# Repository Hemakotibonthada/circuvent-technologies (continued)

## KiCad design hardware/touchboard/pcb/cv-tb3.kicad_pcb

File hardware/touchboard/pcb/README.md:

# Touch Switchboard PCB - KiCad project + fab checklist

Design source: SCHEMATIC.md (netlist) + BOM.csv. Open cv-tb3.kicad_pro in KiCad, capture, lay out, export.

## Board spec
- 2-layer FR4, 1.6 mm, HASL lead-free, 2 oz copper on mains.
- >= 8 mm creepage / 6 mm clearance mains-to-LV; isolation slots.
- Size target ~ 80 x 60 mm (3-gang plate); 4x M3.
- Touch pads on the top copper under the plate; guard ring around each.

## Pre-fab (DFM) checklist
- [ ] ERC/DRC clean at fab rules; mains clearances as keepout
- [x] **Metering isolation resolved** — U6 runs on MTR_VDD/MTR_GND from T1's
      third winding, and CF/CF1/SEL cross through U7/U8/U9. No SELV net
      reaches the metering chip.
- [ ] Confirm T1's third winding (pins 7-8) is specified to the winding house
      with the same reinforced insulation as the main secondary
- [ ] Only T1, CY1, U3/U4/U5 and U7/U8/U9 cross the barrier — check the plot
- [ ] Fuse + MOV at entry; single L-bus to all three relay COMs
- [ ] Kelvin sense pair on Rsh, short and paired
- [ ] Per-gang derating on silk; total <= fuse/PSU/copper
- [ ] Test points: 5V, 3V3, GND, IO25/26/33, IO4/15/13 (touch)
- [ ] UART/EN/IO0 pads for the flashing jig; fiducials

## Export for fab / assembly
- [ ] Gerbers + Excellon -> gerbers/; IPC-356 netlist
- [ ] BOM (BOM.csv) + CPL/centroid; PDF assembly + 3D STEP
- [ ] Order boards + stencil

## Bring-up (EVT)
- [ ] Rails before ESP32; flash test firmware over jig
- [ ] All three relays click + switch; touch pads toggle offline
- [ ] Backlight dims across the full 0-100 range
- [ ] Metering reads V/A/W/PF against a reference load
- [ ] Cloud sync self-test; schedule fires

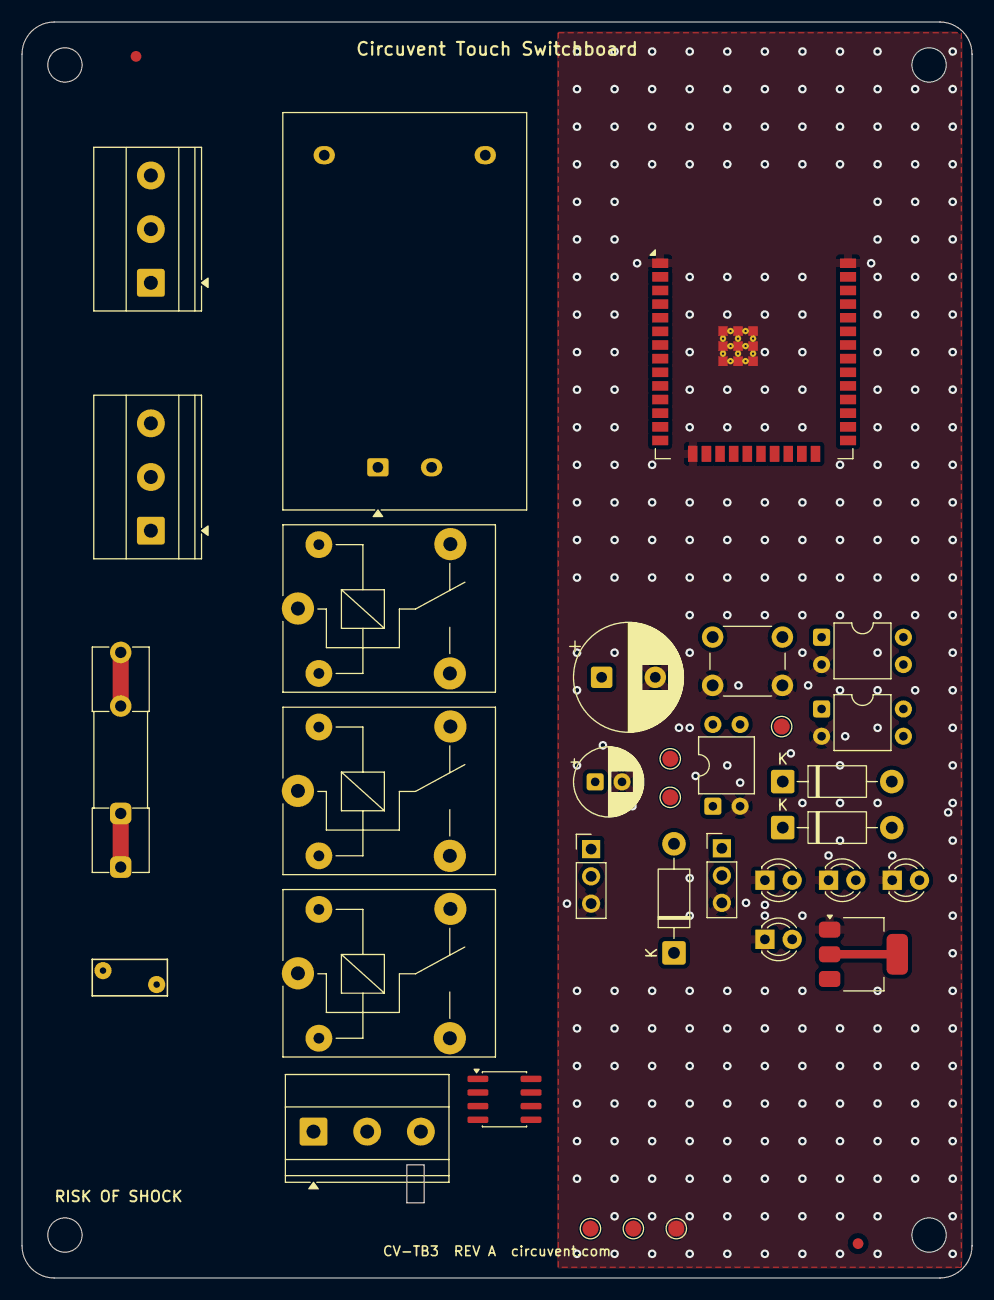
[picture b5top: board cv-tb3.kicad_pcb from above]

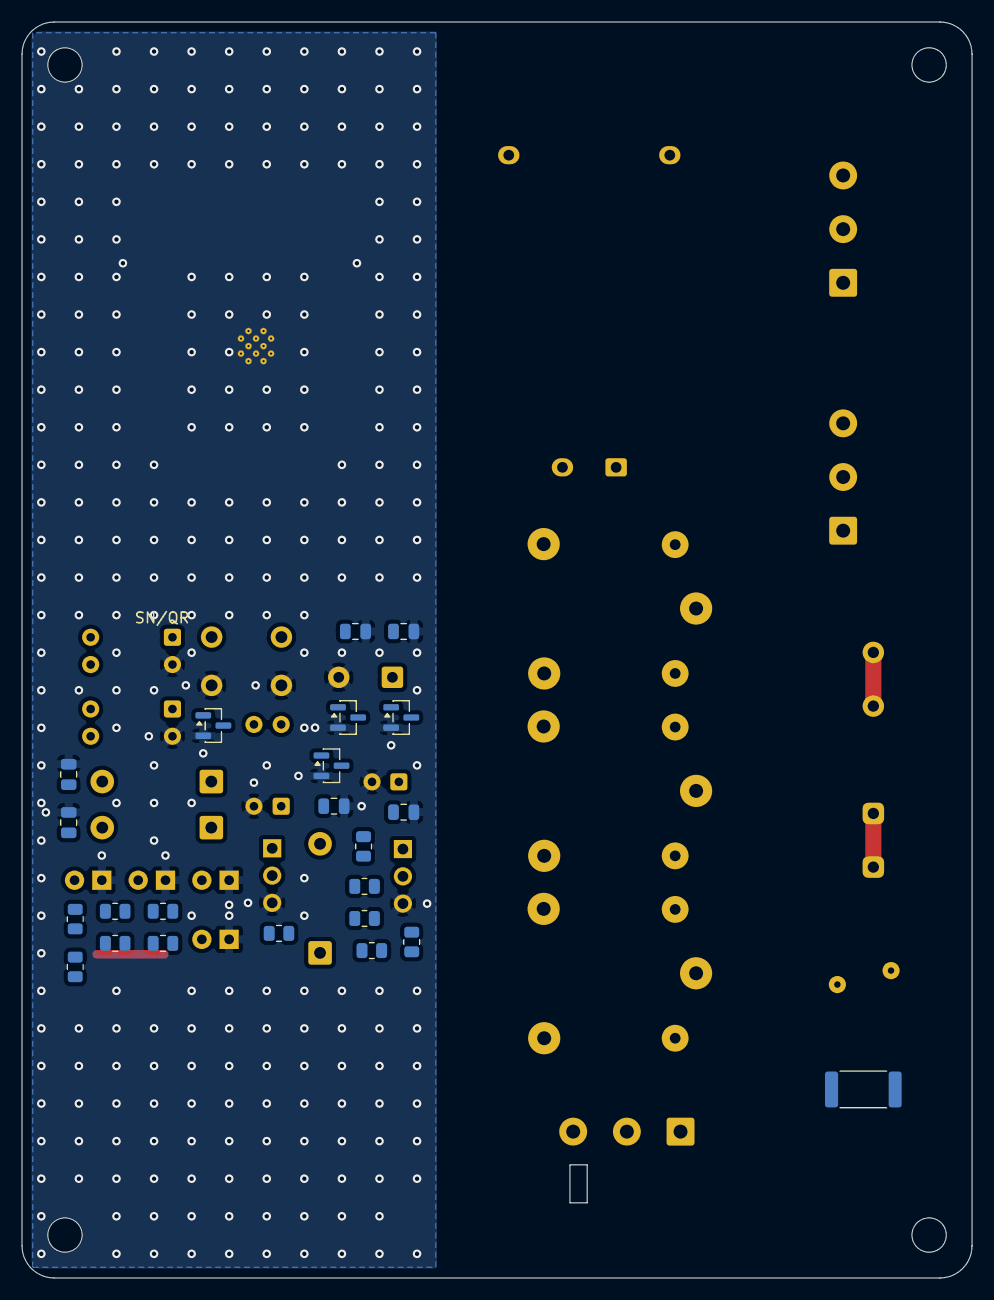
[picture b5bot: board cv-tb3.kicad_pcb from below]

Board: 2 copper layers, 88.5 x 117.0 mm, 62 parts (23 on the bottom side), 39 nets.

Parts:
C1: 470uF/10V; CP_Radial_D10.0mm_P5.00mm
C2: 100uF/6.3V; CP_Radial_D6.3mm_P2.50mm
C3, C4, C5, C6, C7, C8: 100nF; C_0805_2012Metric
D1, D2, D3: 1N4007; D_DO-41_SOD81_P10.16mm_Horizontal
F1: 6A slow-blow; Fuseholder_Clip-5x20mm_Littelfuse_111_Inline_P20.00x5.00mm_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
FID1, FID2: Fiducial; Fiducial_1mm_Mask2mm
J1: 2P 5.08mm; TerminalBlock_Phoenix_MKDS-1,5-3_1x03_P5.00mm_Horizontal
J2, J3: 3P 5.08mm; TerminalBlock_Phoenix_MKDS-1,5-3_1x03_P5.00mm_Horizontal
J4: 3P 2.54mm; PinHeader_1x03_P2.54mm_Vertical
JP: 3P 2.54mm; PinHeader_1x03_P2.54mm_Vertical
K1, K2, K3: SRD-05VDC-SL-C; Relay_SPDT_SANYOU_SRD_Series_Form_C
LED0: Green 3mm; LED_D3.0mm
LED1, LED2, LED3: Blue 3mm; LED_D3.0mm
MH1, MH2, MH3, MH4: MountingHole; MountingHole_3.2mm_M3
PS1: HLK-PM03 (5V 3W); Converter_ACDC_Hi-Link_HLK-PMxx
Q1, Q2, Q3, Q4: S8050; SOT-23
R1, R2, R3, R4, R5, R6, R7, R8, R9, R10, R11, R12: 10k/1k/330; R_0805_2012Metric
RV1: 7D471K; RV_Disc_D7mm_W3.4mm_P5mm
Rsh: 1mR 2W; R_2512_6332Metric
SW1: 6mm tactile; SW_PUSH_6mm_H5mm
TP1, TP2, TP3: Copper pad + decal; TestPoint_Pad_D1.5mm
TP4: +5V; TestPoint_Pad_D1.5mm
TP5: +3V3; TestPoint_Pad_D1.5mm
TP6: GND; TestPoint_Pad_D1.5mm
U1: ESP32-WROOM-32E (4MB); ESP32-WROOM-32E
U2: AMS1117-3.3; SOT-223-3_TabPin2
U3, U4, U5: PC817; DIP-4_W7.62mm
U6: BL0937 / HLW8012; SOIC-8_3.9x4.9mm_P1.27mm

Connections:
+3V3: C2.1, C3.1, C4.1, C5.1, C6.1, C7.1, C8.1, R8.1, R9.1, TP5.1, U1.2, U2.2, U6.8
+5V: C1.1, D1.1, D2.1, D3.1, J3.1, J4.1, K1.2, K2.2, K3.2, PS1.4, TP4.1, U2.3, U3.4, U4.4, U5.4
AC_L: F1.1, J1.1
AC_LOAD: J1.3, J2.1, Rsh.2, U6.3
AC_L_FUSED: F1.2, K1.1, K2.1, K3.1, PS1.1, RV1.1, U6.1
AC_N: J1.2, J2.3, J3.3, PS1.2, RV1.2
BACKLIGHT: R7.1, U1.29
BACKLIGHT_B: Q4.1, R7.2
BACKLIGHT_OUT: J4.2, Q4.3
BTN_PIN: SW1.1, U1.25
EN: R8.2, U1.3
GND: C1.2, C2.2, C3.2, C4.2, C5.2, C6.2, C7.2, C8.2, J4.3, JP.3, LED0.1, LED1.1, LED2.1, LED3.1, PS1.3, Q1.2, Q2.2, Q3.2, Q4.2, SW1.2, TP6.1, U1.1, U1.15, U1.38, U1.39, U2.1, U3.2, U4.2, U5.2, U6.4
LED0_A: LED0.2, R9.2
MTR_CF: U1.6, U6.5
MTR_CF1: U1.7, U6.6
MTR_SEL: U1.30, U6.7
RELAY1: R1.1, R2.1, U1.10
RELAY1_A: LED1.2, R2.2
RELAY1_COIL: D1.2, K1.5, Q1.3
RELAY1_DRV: Q1.1, U3.3
RELAY1_OPT: R1.2, U3.1
RELAY1_SW: K1.3, Rsh.1, U6.2
RELAY2: R3.1, R4.1, U1.11
RELAY2_A: LED2.2, R4.2
RELAY2_COIL: D2.2, K2.5, Q2.3
RELAY2_DRV: Q2.1, U4.3
RELAY2_OPT: R3.2, U4.1
RELAY2_SW: J2.2, K2.3
RELAY3: R5.1, R6.1, U1.9
RELAY3_A: LED3.2, R6.2
RELAY3_COIL: D3.2, K3.5, Q3.3
RELAY3_DRV: Q3.1, U5.3
RELAY3_OPT: R5.2, U5.1
RELAY3_SW: J3.2, K3.3
TOUCH1__T0: TP1.1, U1.26
TOUCH2__T3: TP2.1, U1.23
TOUCH3__T4: TP3.1, U1.16
UART_RX: JP.2, U1.34
UART_TX: JP.1, U1.35

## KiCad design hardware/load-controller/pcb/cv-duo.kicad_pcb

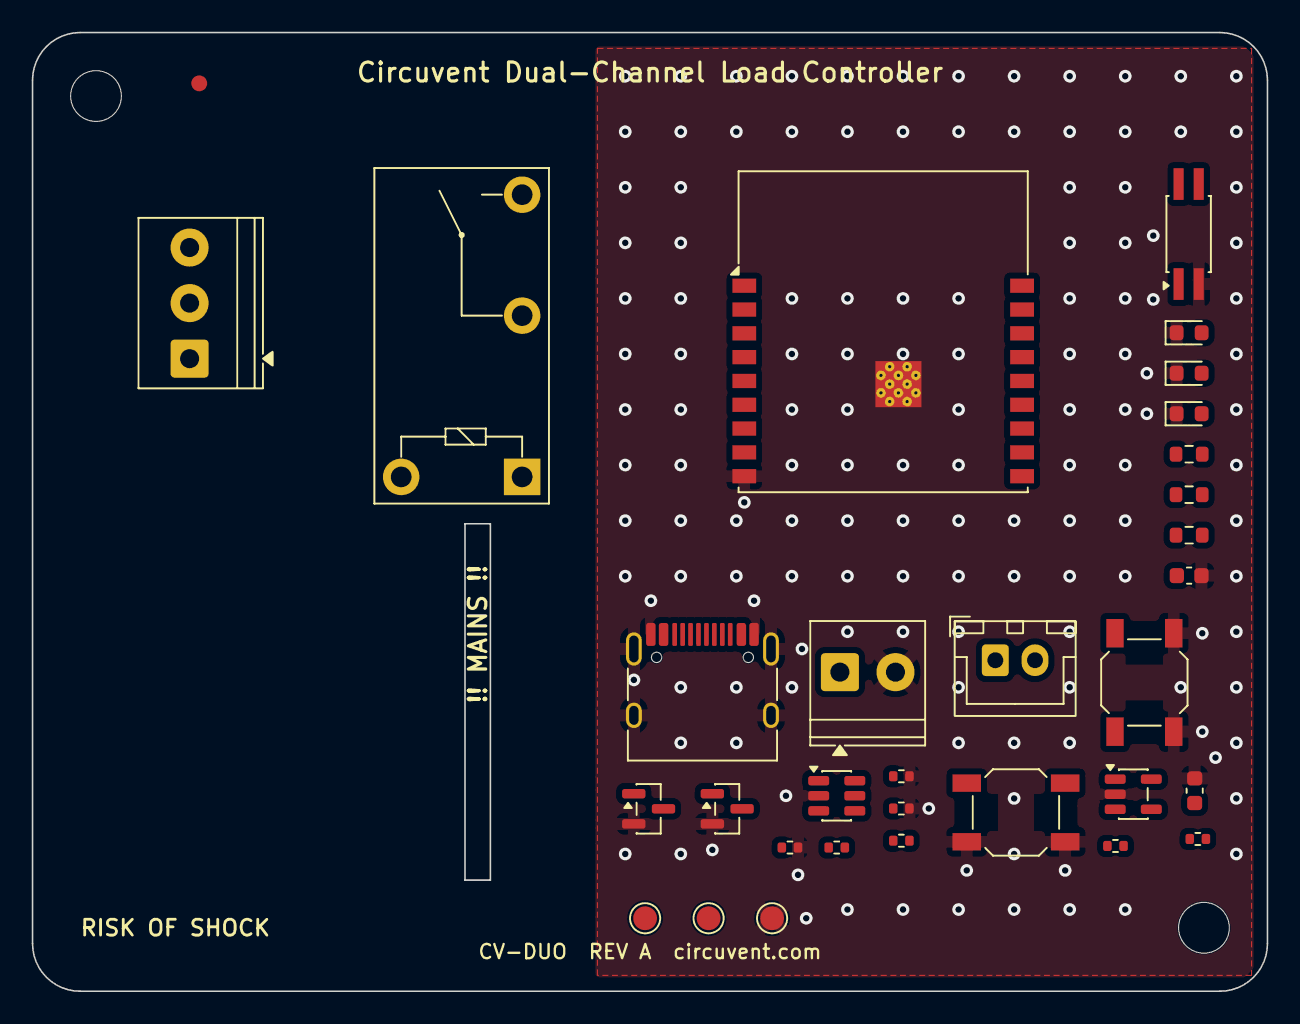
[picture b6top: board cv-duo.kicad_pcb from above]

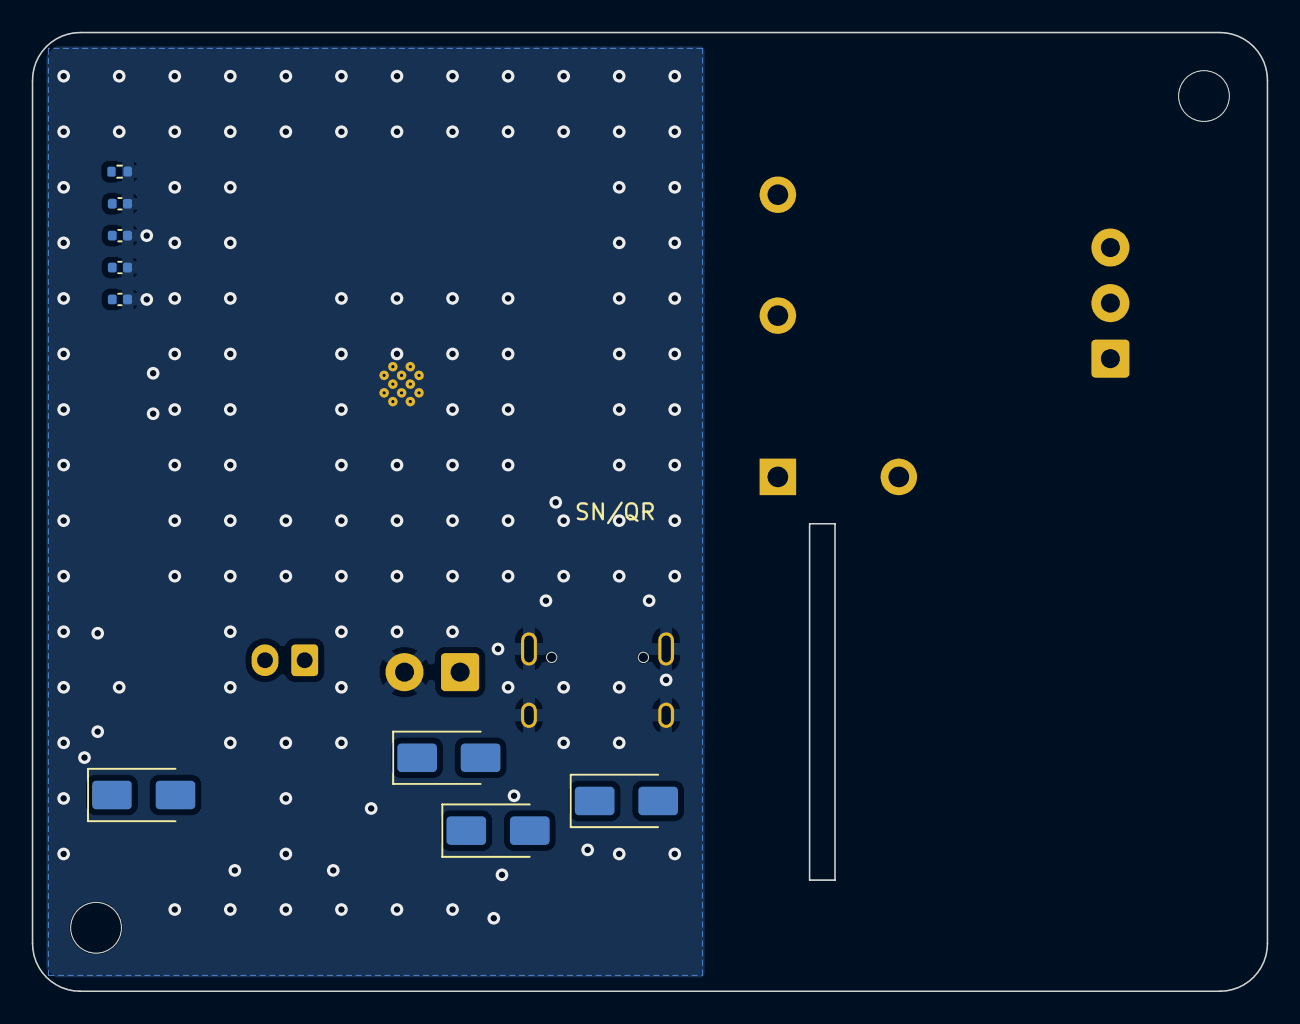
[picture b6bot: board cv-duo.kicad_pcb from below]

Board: 2 copper layers, 77.8 x 60.4 mm, 43 parts (9 on the bottom side), 25 nets, no tracks yet.

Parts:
C1, C3: 10u; C_0603_1608Metric
C2, C4, C5, C6: 100n; C_0402_1005Metric
D1, D2, D3, D4: SS14; D_SMA
FID1: Fiducial; Fiducial_1mm_Mask2mm
J1: USB-C 16P receptacle; USB_C_Receptacle_HRO_TYPE-C-31-M-12
J2: 5V DC input; TerminalBlock_Phoenix_PT-1,5-2-3.5-H_1x02_P3.50mm_Horizontal
J3: Relay load out (mains); TerminalBlock_Phoenix_PT-1,5-3-3.5-H_1x03_P3.50mm_Horizontal
J4: Pulse output; JST_XH_B2B-XH-A_1x02_P2.50mm_Vertical
K1: Omron G5Q-1A 5VDC; Relay_SPST_Omron-G5Q-1A
LED1: Green; LED_0603_1608Metric
LED2: Red; LED_0603_1608Metric
LED3: Blue; LED_0603_1608Metric
MH1, MH2: MountingHole; MountingHole_3.2mm_M3
PC1: LTV-817S; SO-4_4.4x2.3mm_P1.27mm
Q1, Q2: AO3400A; SOT-23
R1, R2: 5.1k; R_0402_1005Metric
R3, R4, R6: 10k; R_0402_1005Metric
R5: 1k; R_0402_1005Metric
R7: 100R; R_0402_1005Metric
R8: 100k; R_0402_1005Metric
R9, R10, R11: 1k; R_0603_1608Metric
SW1: RESET tactile; SW_SPST_SKQG_WithoutStem
SW2: BOOT tactile; SW_SPST_SKQG_WithoutStem
TP1: +5V; TestPoint_Pad_D1.5mm
TP2: +3V3; TestPoint_Pad_D1.5mm
TP3: GND; TestPoint_Pad_D1.5mm
U1: ESP32-C3-WROOM-02 (4MB); ESP32-C3-WROOM-02
U2: AP2112K-3.3; SOT-23-5
U3: USBLC6-2SC6; SOT-23-6

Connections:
+3V3: C3.1, C4.1, C5.1, PC1.4, R3.1, R4.1, R9.1, TP2.1, U1.1, U2.5
+5V: C1.1, C2.1, D1.1, D2.1, D3.1, D4.1, J4.1, K1.1, TP1.1, U2.1, U2.3
BOOT_N: R4.2, SW2.1, U1.8
CC1: J1.A5, R1.1
CC2: J1.B5, R2.1
EN: C6.1, R3.2, SW1.1, U1.2
GND: C1.2, C2.2, C3.2, C4.2, C5.2, C6.2, J1.A1, J1.A12, J1.B1, J1.B12, J1.SH, J2.2, LED1.1, LED2.1, LED3.1, PC1.2, Q1.2, Q2.2, R1.2, R2.2, R6.2, R8.2, SW1.2, SW2.2, TP3.1, U1.9, U1.19, U2.2, U3.2
LOAD_COM: J3.1, K1.2
LOAD_NO: J3.2, K1.3
PULSE_GATE: Q2.1, R7.2, R8.1
PULSE_LED: R11.1, U1.6
PULSE_LED_A: LED3.2, R11.2
PULSE_OUT: D4.2, J4.2, Q2.3
PULSE_PWM: R7.1, U1.4
PWR_LED_A: LED1.2, R9.2
RELAY_COIL: D3.2, K1.5, Q1.3
RELAY_CTL: R5.1, U1.3
RELAY_GATE: PC1.3, Q1.1, R6.1
RELAY_LED: R10.1, U1.5
RELAY_LED_A: LED2.2, R10.2
RELAY_OPT: PC1.1, R5.2
USB_D_N: J1.A7, J1.B7, U1.13, U3.1, U3.6
USB_D_P: J1.A6, J1.B6, U1.14, U3.3, U3.4
VBUS: D1.2, J1.A4, J1.A9, J1.B4, J1.B9, U3.5
VIN_EXT: D2.2, J2.1

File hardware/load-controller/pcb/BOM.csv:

Ref,Qty,Value/Part,Package,Description,Notes
U1,1,ESP32-C3-WROOM-02 (4MB),ESP32-C3,Wi-Fi/BLE RISC-V MCU module,Native USB on IO18/IO19
U2,1,AP2112K-3.3,SOT-23-5,5V -> 3.3V 600mA LDO,MCU rail
U3,1,USBLC6-2SC6,SOT-23-6,USB ESD protection array,On D+/D-/VBUS
PC1,1,LTV-817S,SO-4,Optocoupler CTR 50-600%,Isolates MCU from coil driver
K1,1,Omron G5Q-1A 5VDC,relay G5Q,SPST-NO 10A power relay,Channel 1 - switches the mains load
Q1,1,AO3400A,SOT-23,N-channel MOSFET 30V 5.7A,Relay coil driver
Q2,1,AO3400A,SOT-23,N-channel MOSFET 30V 5.7A,Channel 2 PWM low-side switch
D1,1,SS14,SMA,Schottky 40V 1A,USB VBUS OR-ing diode
D2,1,SS14,SMA,Schottky 40V 1A,Terminal 5V OR-ing diode
D3,1,SS14,SMA,Schottky 40V 1A,K1 coil flyback clamp
D4,1,SS14,SMA,Schottky 40V 1A,Channel 2 inductive clamp
J1,1,USB-C 16P receptacle,USB-C,5V power + native USB,Programming and debug
J2,1,5V DC input,term 3.5/2,3.5mm screw terminal 2P,Auxiliary 5V supply
J3,1,Relay load out (mains),term 3.5/3,3.5mm screw terminal 3P,COM / NO / PE - mains rated
J4,1,Pulse output,JST-XH/2,JST-XH 2-pin header,Channel 2 PWM out
SW1,1,RESET tactile,tactile SMD,3x4x2mm SMD tactile switch,Pulls EN low
SW2,1,BOOT tactile,tactile SMD,3x4x2mm SMD tactile switch,Pulls IO9 low
LED1,1,Green,0603LED,Power indicator,Always on from 3V3
LED2,1,Red,0603LED,Relay energised,IO6
LED3,1,Blue,0603LED,Pulse active,IO7
R1,1,5.1k,0402,USB-C CC1 pulldown,Sink advertisement
R2,1,5.1k,0402,USB-C CC2 pulldown,Sink advertisement
R3,1,10k,0402,EN pull-up,Reset RC with C6
R4,1,10k,0402,IO9 boot pull-up,
R5,1,1k,0402,PC1 LED series resistor,From IO4
R6,1,10k,0402,Q1 gate pulldown,Fail-safe off
R7,1,100R,0402,Q2 gate series resistor,Limits ringing
R8,1,100k,0402,Q2 gate pulldown,Fail-safe off
R9,1,1k,0603,LED1 series resistor,
R10,1,1k,0603,LED2 series resistor,
R11,1,1k,0603,LED3 series resistor,
C1,1,10u,0603C,Bulk on 5V rail,
C2,1,100n,0402C,HF decoupling on 5V,
C3,1,10u,0603C,Bulk on 3V3 rail,
C4,1,100n,0402C,LDO output decoupling,
C5,1,100n,0402C,ESP32-C3 decoupling,
C6,1,100n,0402C,EN debounce capacitor,With R3

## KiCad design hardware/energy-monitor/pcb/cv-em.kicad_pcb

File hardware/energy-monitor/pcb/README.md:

# Energy Monitor PCB - KiCad project + fab checklist

Design source: SCHEMATIC.md (netlist) + BOM.csv. Open cv-em.kicad_pro in KiCad 8, capture, lay out, export.

## Board spec
- 2-layer FR4, 1.6 mm, HASL lead-free.
- Isolated mains PSU island (PSU variant); analog front-end on LV side.
- Size target ~ 50 x 45 mm; 2x M3.
- Keep the burden + bias tight to the jack; guard-ring the ADC node.

## Pre-fab (DFM) checklist
- [ ] ERC/DRC clean at fab rules
- [ ] Burden always across the CT (no open secondary)
- [ ] Bias network + ADC guard verified
- [ ] Test points: 5V, 3V3, GND, IO34 (+ IO35 add-on)
- [ ] UART/EN/IO0 pads for the flashing jig; fiducials

## Export for fab / assembly
- [ ] Gerbers + Excellon -> gerbers/; IPC-356 netlist
- [ ] BOM (BOM.csv) + CPL/centroid; PDF assembly + 3D STEP
- [ ] Order boards + stencil

## Bring-up (EVT)
- [ ] Rail before ESP32; flash test firmware over jig
- [ ] Irms reads against a known load; calibrate CT_CAL
- [ ] kWh accumulates over time; cost estimate matches
- [ ] Cloud sync self-test; high-usage alert fires

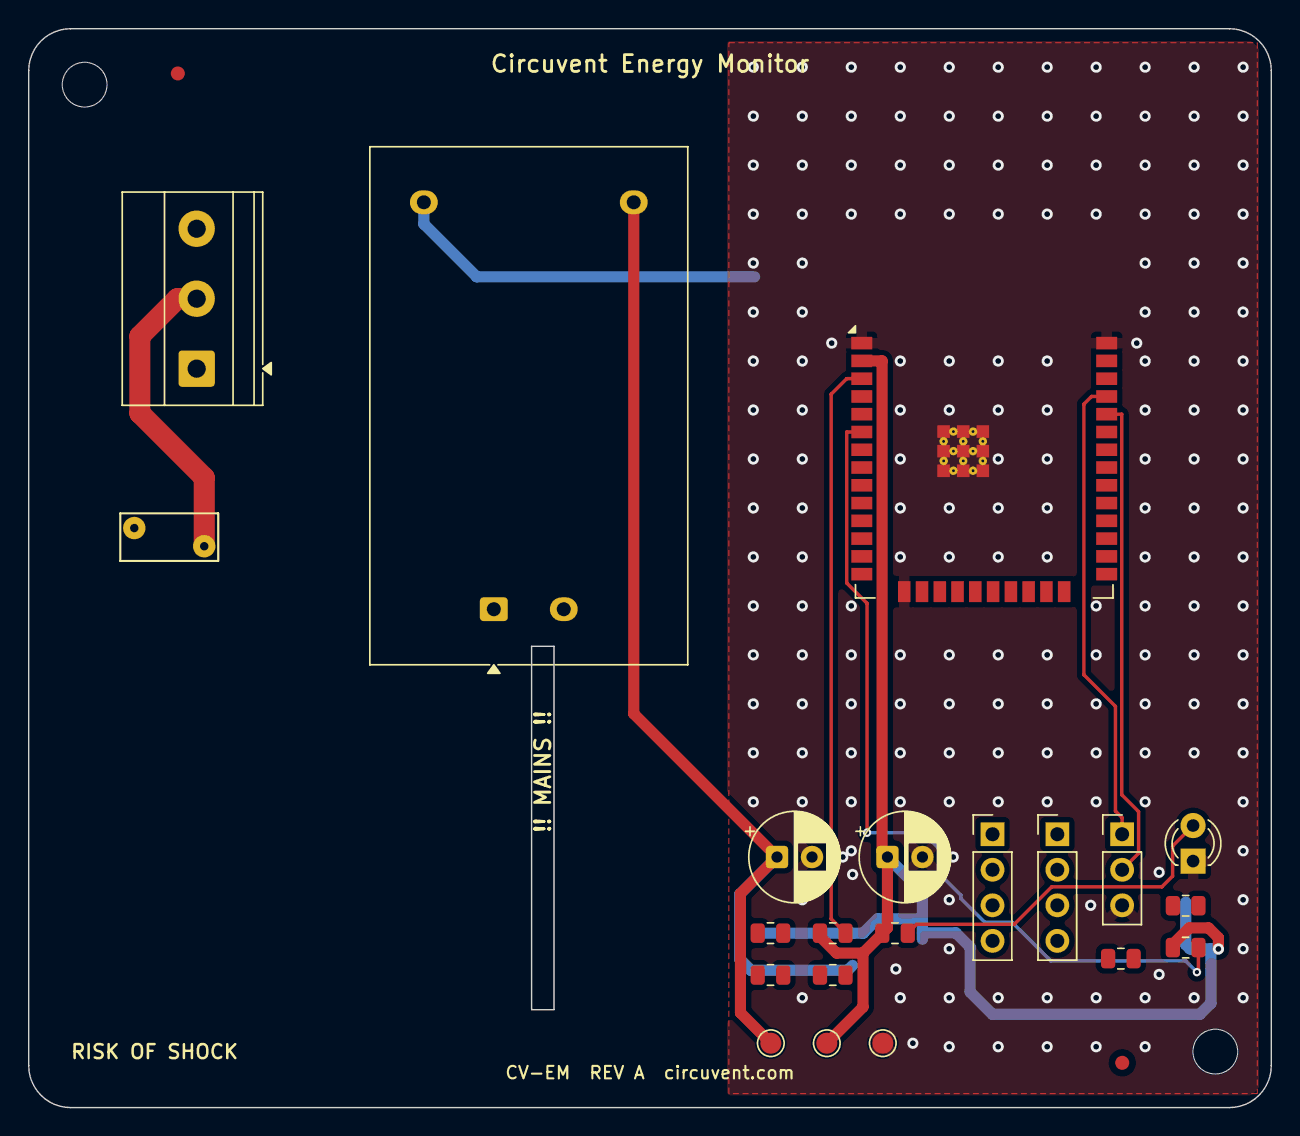
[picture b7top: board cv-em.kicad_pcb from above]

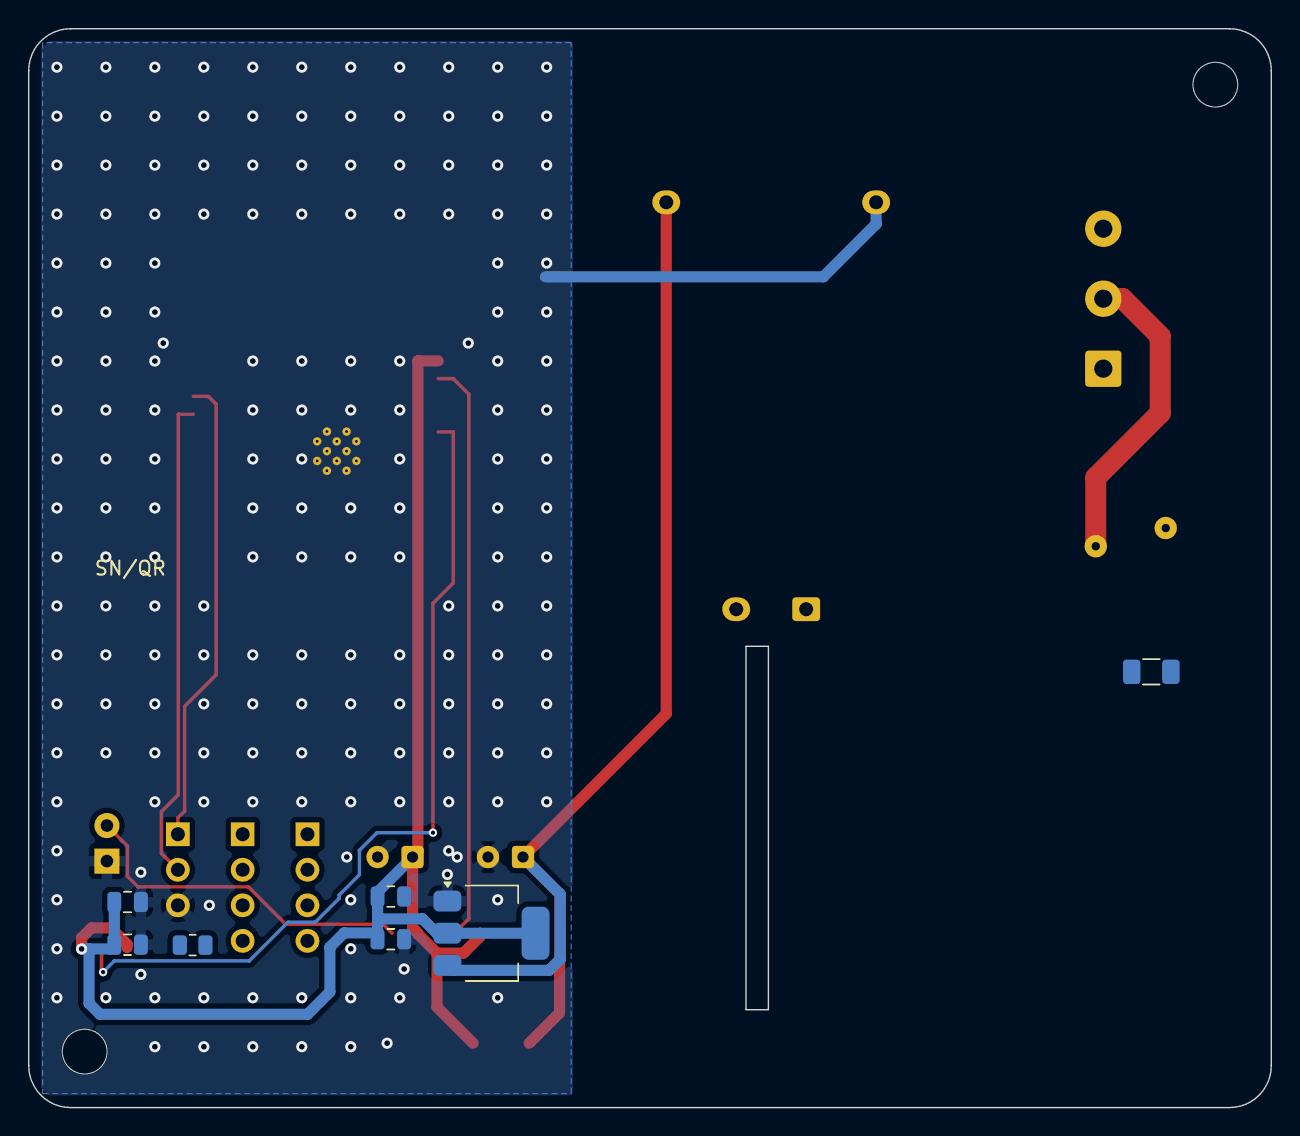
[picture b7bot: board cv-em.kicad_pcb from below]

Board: 2 copper layers, 88.8 x 77.1 mm, 32 parts (7 on the bottom side), 11 nets.

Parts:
C1, C2: 100uF; CP_Radial_D6.3mm_P2.50mm
C3, C4, C5: 100nF; C_0805_2012Metric
CT1: SCT-013-030; PinHeader_1x04_P2.54mm_Vertical
Cb: 10uF; C_0805_2012Metric
F1: 500mA; Fuse_1206_3216Metric
FID1, FID2: Fiducial; Fiducial_1mm_Mask2mm
J3: 3.5mm jack; TerminalBlock_Phoenix_MKDS-1,5-3_1x03_P5.00mm_Horizontal
JP: 3P 2.54mm; PinHeader_1x03_P2.54mm_Vertical
LED0: Green 3mm; LED_D3.0mm
MH1, MH2: MountingHole; MountingHole_3.2mm_M3
PS1: HLK-PM01 (5V 3W); Converter_ACDC_Hi-Link_HLK-PMxx
R1, R2, R3, R4, R5, R6: 10k/330; R_0805_2012Metric
RV1: 7D471K; RV_Disc_D7mm_W3.4mm_P5mm
Rb: 33R 0.5%; R_0805_2012Metric
Rbias1, Rbias2: 10k 0.1%; R_0805_2012Metric
TP1: +5V; TestPoint_Pad_D1.5mm
TP2: +3V3; TestPoint_Pad_D1.5mm
TP3: GND; TestPoint_Pad_D1.5mm
U1: ESP32-WROOM-32E (4MB); ESP32-WROOM-32E
U2: AMS1117-3.3; SOT-223-3_TabPin2
ZMPT1: ZMPT101B module; PinHeader_1x04_P2.54mm_Vertical

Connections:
+3V3: C2.1, C3.1, C4.1, C5.1, Cb.1, R1.1, R2.1, R3.1, TP2.1, U1.2, U2.2
+5V: C1.1, PS1.4, TP1.1, U2.3
AC_L: F1.1, J3.1
AC_L_FUSED: F1.2, PS1.1, RV1.1
AC_N: J3.2, PS1.2, RV1.2
CT_PIN: R3.2, U1.6
EN: R1.2, U1.3
GND: C1.2, C2.2, C3.2, C4.2, C5.2, Cb.2, JP.3, LED0.1, PS1.3, TP3.1, U1.1, U1.15, U1.38, U1.39, U2.1
LED0_A: LED0.2, R2.2
UART_RX: JP.2, U1.34
UART_TX: JP.1, U1.35

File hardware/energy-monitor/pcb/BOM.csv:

Ref,Qty,Value/Part,Package,Description,Notes
U1,1,ESP32-WROOM-32E (4MB),SMD module,Wi-Fi/BLE MCU module,Main controller
PS1,1,HLK-PM01 (5V 3W),SIP,230VAC -> 5VDC isolated PSU,Or USB-C variant
U2,1,AMS1117-3.3,SOT-223,5V -> 3.3V LDO,MCU + analog rail
CT1,1,SCT-013-030,clamp,Clamp-on current transformer,In the box
J3,1,3.5mm jack,THT,CT input,
Rb,1,33R 0.5%,0805,Burden resistor,Across CT secondary
Rbias,2,10k 0.1%,0805,Mid-rail bias,1.65 V node
Cb,1,10uF,0805,Bias decouple,
ZMPT1,1,ZMPT101B module,module,Voltage sense (optional),True power/PF
RV1,1,7D471K,disc,MOV 470V,PSU variant
F1,1,500mA,1206 fuse,Mains fuse,PSU variant
LED0,1,Green 3mm,THT,Power/online,
JP,1,3P 2.54mm,header,UART (TX/RX/GND),Factory flashing
R1-R6,6,10k/330,0805,Pull/LED resistors,
C1-C2,2,100uF,electrolytic,5V + 3.3V,
C3-C5,3,100nF,0805,Decoupling,
PCB,1,2-layer FR4 1.6mm,-,Main board,Isolated PSU island
ENC,1,ABS DIN/wall box (UL94 V-0),-,Monitor housing,3.5mm CT jack

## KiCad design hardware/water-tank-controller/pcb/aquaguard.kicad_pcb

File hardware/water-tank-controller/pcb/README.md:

# AquaGuard PCB - KiCad project + fab checklist

Design source lives in `SCHEMATIC.md` (netlist) and `BOM.csv`. Open
`aquaguard.kicad_pro` in **KiCad 8**, capture the schematic from `SCHEMATIC.md`,
lay out, then export manufacturing files.

## Board spec
- 2-layer FR4, 1.6 mm, HASL lead-free, green mask, white silk.
- Mains section: 2 oz copper, >= 8 mm creepage / 6 mm clearance to LV, isolation slot.
- Size target ~ 80 x 60 mm, 4x M3 mounting holes.

## Pre-fab (DFM) checklist
- [ ] ERC clean (no unconnected / power-flag errors)
- [ ] DRC clean at fab rules (6/6 mil min; mains clearances enforced as keepout)
- [ ] Fuse + MOV at mains entry; isolation slot milled under opto/PSU
- [ ] Test points: 5V, 3V3, GND, IO26 (relay), IO25/27 (US), IO32/33 (floats)
- [ ] UART/EN/IO0 pads exposed for the flashing jig
- [ ] Silk: model, rating, serial/QR box, shock warning, CE/BIS mark area
- [ ] Fiducials for PnP; panelize (2x2) with mouse-bites for assembly

## Export for fab / assembly
- [ ] Gerbers (RS-274X) + Excellon drill -> `gerbers/`
- [ ] IPC-356 netlist, BOM (`BOM.csv`), CPL/centroid (`pos.csv`)
- [ ] PDF assembly drawing + 3D STEP for enclosure fit
- [ ] Send to fab (JLCPCB/PCBPower); order stencil for paste

## Bring-up (EVT)
- [ ] Power rails (5V, 3V3) before populating ESP32
- [ ] Flash test firmware over UART jig; verify relay click drives contactor
- [ ] Ultrasonic distance sane; float inputs read; buzzer + LEDs
- [ ] End-of-line: cloud sync self-test (unit appears in registry)

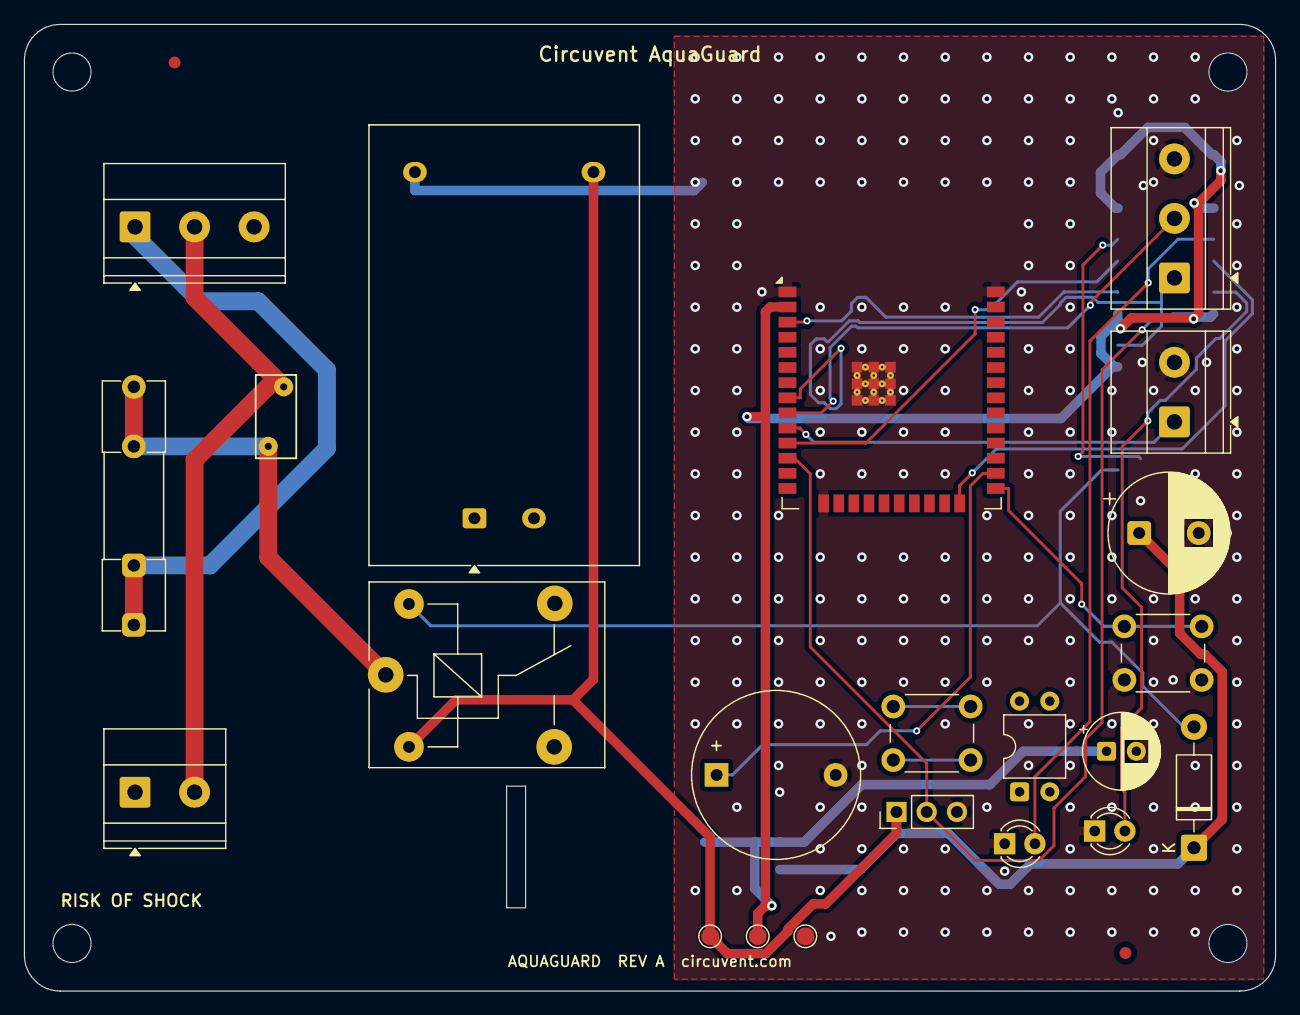
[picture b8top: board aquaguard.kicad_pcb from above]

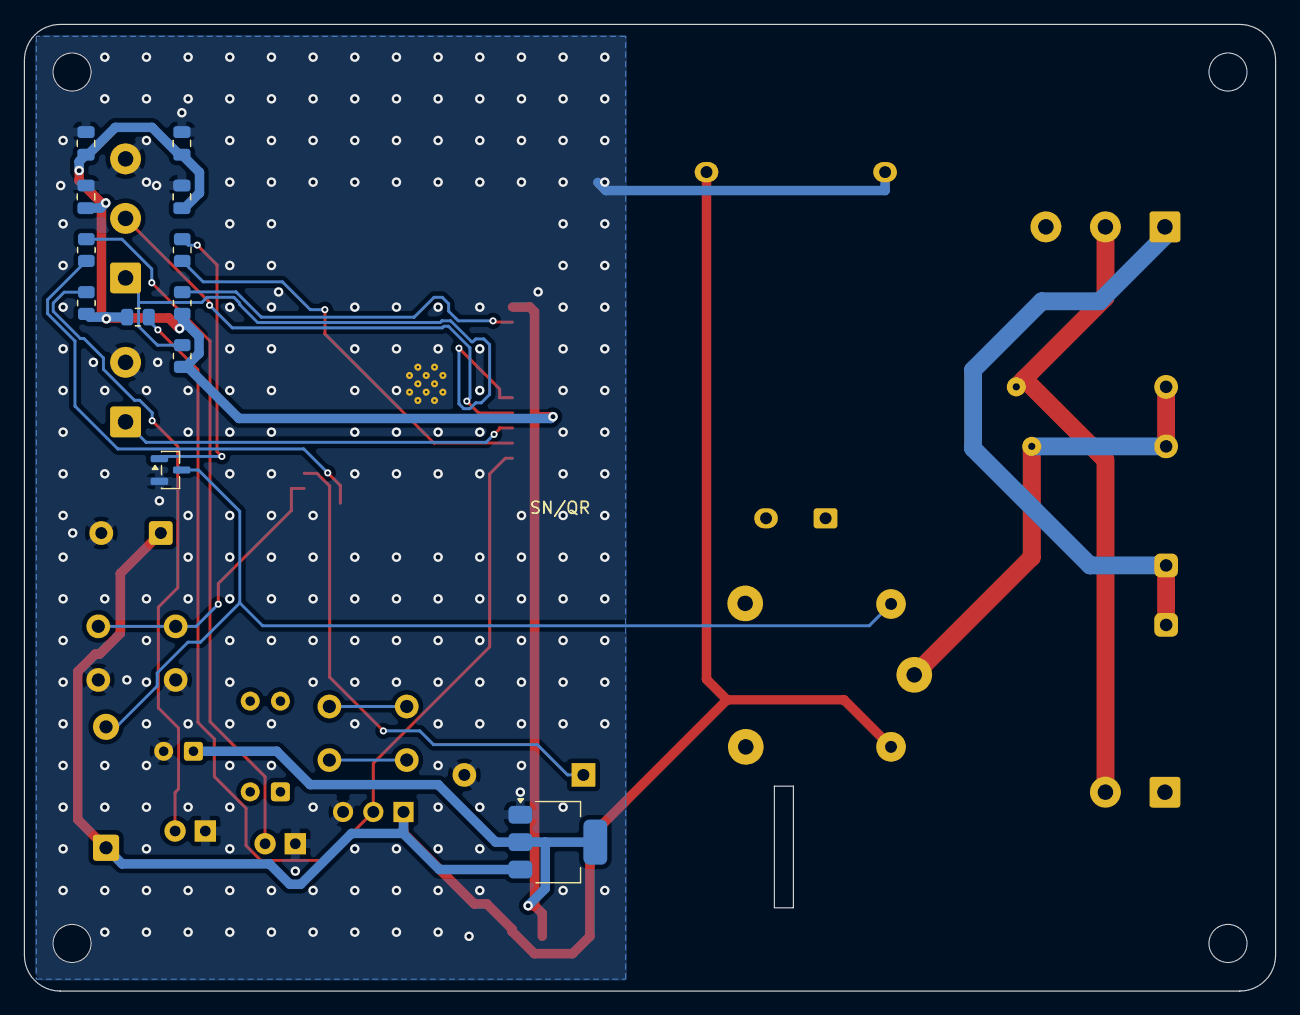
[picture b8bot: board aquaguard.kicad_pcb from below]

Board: 2 copper layers, 105.1 x 81.2 mm, 40 parts (12 on the bottom side), 20 nets.

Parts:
C1: 470uF/10V; CP_Radial_D10.0mm_P5.00mm
C2: 100uF/6.3V; CP_Radial_D6.3mm_P2.50mm
C3, C4, C5, C6: 100nF; C_0805_2012Metric
D1: 1N4007; D_DO-41_SOD81_P10.16mm_Horizontal
F1: 2A slow-blow; Fuseholder_Clip-5x20mm_Littelfuse_111_Inline_P20.00x5.00mm_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
FB1: BUZZER 5V; Buzzer_D14mm_H7mm_P10mm
FID1, FID2: Fiducial; Fiducial_1mm_Mask2mm
J1: 2P 5.08mm; TerminalBlock_Phoenix_MKDS-1,5-3_1x03_P5.00mm_Horizontal
J2: 2P 5.08mm; TerminalBlock_Phoenix_MKDS-1,5-2_1x02_P5.00mm_Horizontal
J3: 4P 3.5mm; TerminalBlock_Phoenix_MKDS-1,5-2_1x02_P5.00mm_Horizontal
J4: 3P 3.5mm; TerminalBlock_Phoenix_MKDS-1,5-3_1x03_P5.00mm_Horizontal
J5: 3P 2.54mm; PinHeader_1x03_P2.54mm_Vertical
K1: SRD-05VDC-SL-C; Relay_SPDT_SANYOU_SRD_Series_Form_C
LED1: Green 3mm; LED_D3.0mm
LED2: Red 3mm; LED_D3.0mm
MH1, MH2, MH3, MH4: MountingHole; MountingHole_3.2mm_M3
PS1: HLK-PM01; Converter_ACDC_Hi-Link_HLK-PMxx
Q1: S8050; SOT-23
R1, R2, R3, R4, R5, R6: 10k/1k/330; R_0805_2012Metric
RV1: 7D471K; RV_Disc_D7mm_W3.4mm_P5mm
SW1, SW2: Tactile 6mm; SW_PUSH_6mm_H5mm
TP1: +5V; TestPoint_Pad_D1.5mm
TP2: +3V3; TestPoint_Pad_D1.5mm
TP3: GND; TestPoint_Pad_D1.5mm
U1: ESP32-WROOM-32E (4MB); ESP32-WROOM-32E
U2: AMS1117-3.3; SOT-223-3_TabPin2
U3: PC817; DIP-4_W7.62mm

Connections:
+3V3: C2.1, C3.1, C4.1, C5.1, C6.1, R3.1, R4.1, R5.1, R6.1, TP2.1, U1.2, U2.2
+5V: C1.1, D1.1, J5.1, K1.2, PS1.4, TP1.1, U2.3
AC_L: F1.1, J1.1
AC_L_FUSED: F1.2, K1.1, PS1.1, RV1.1
AC_N: J1.2, J2.2, PS1.2, RV1.2
BTN_PIN: SW1.1, U1.25
BUZZER_PIN: FB1.1, U1.26
EN: R3.2, U1.3
FLOAT_HIGH: J4.2, U1.9
FLOAT_LOW: J4.1, R6.2, U1.8
GND: C1.2, C2.2, C3.2, C4.2, C5.2, C6.2, FB1.2, J3.2, J4.3, J5.3, LED1.1, LED2.1, PS1.3, Q1.2, SW1.2, TP3.1, U1.1, U1.15, U1.38, U1.39, U2.1
LED1_A: LED1.2, R4.2
LED_PIN: R2.1, U1.24
LED_PIN_A: LED2.2, R2.2
MOTOR_RELAY: R1.1, U1.11
MOTOR_RELAY_B: Q1.1, R1.2
MOTOR_RELAY_COIL: D1.2, K1.5, Q1.3
MOTOR_RELAY_SW: J2.1, K1.3
US_ECHO: J5.2, R5.2, U1.12
US_TRIG: J3.1, U1.10

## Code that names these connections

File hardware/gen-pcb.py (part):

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            out_nets.append(AC_LOAD)

    # BL0937 / HLW8012 family (SOP-8): 1=V2P 2=V1P 3=V1N 4=GND 5=CF 6=CF1
    # 7=SEL 8=VDD. Sense pins straddle the shunt; CF/CF1/SEL follow the doc.
    meter = next((r for r in by_ref
                  if key_of(r) in ("soic8", "sop") and r not in used), None)
    if meter:
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            if "T1" in by_ref:
                nl.tie_many("T1", {7: "MTR_SEC", 8: MTR_GND})
            if "PD8" in by_ref:
                nl.tie_many("PD8", {1: MTR_VDD, 2: "MTR_SEC"}); used.add("PD8")
            if "PZ6" in by_ref:
                nl.tie_many("PZ6", {1: MTR_VDD, 2: MTR_GND}); used.add("PZ6")
            for ref, i, direction in (("U7", 0, "out"), ("U8", 1, "out"),
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    ("PD2", "S1M 1000V 1A", "SMA", "Bridge rectifier"),
    ("PD3", "S1M 1000V 1A", "SMA", "Bridge rectifier"),
    ("PD4", "S1M 1000V 1A", "SMA", "Bridge rectifier"),
    ("PD5", "UF4007", "SMA", "RCD clamp catch diode"),
    ("PD6", "S1M", "SMA", "Bias winding rectifier"),
    ("PD7", "SS34 40V 3A", "SMA", "Secondary rectifier"),
    ("PR1", "100k", "0805", "RCD snubber resistor"),
    ("PR2", "100k", "0805", "RCD snubber resistor"),
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    ("PR4", "10k", "0805", "Feedback divider upper"),
    ("PR5", "3k3", "0805", "Feedback divider lower"),
    ("PZ1", "4.7uF/400V", "electrolytic", "Bulk / DC link"),
    ("PZ2", "100nF/50V", "0805", "BYPASS pin decoupling"),
    ("PZ3", "1nF/1kV", "0805", "RCD snubber capacitor"),
    ("PZ4", "10uF/50V", "electrolytic", "Bias rail"),
    ("PZ5", "470uF/10V", "electrolytic", "5V output bulk"),
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    w("CX1", {1: hot, 2: AC_N})
    # Bridge: hot and neutral both feed HV+; HV- returns to both.
    w("PD1", {1: HV_P, 2: hot})
    w("PD2", {1: HV_P, 2: AC_N})
    w("PD3", {1: hot, 2: HV_N})
    w("PD4", {1: AC_N, 2: HV_N})
    w("PZ1", {1: HV_P, 2: HV_N})

    w("T1", {1: HV_P, 2: SW_D, 4: BIAS, 5: HV_N, 6: SEC, 10: GND,
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    w("PZ2", {1: "BYPASS", 2: HV_N})

    # RCD clamp: catch at the drain, bleed back to the rail through R//C.
    w("PD5", {1: CLAMP, 2: SW_D})
    w("PZ3", {1: CLAMP, 2: HV_P})
    w("PR1", {1: CLAMP, 2: "CLAMP_MID"})    # in series: ~325 V stands here
    w("PR2", {1: "CLAMP_MID", 2: HV_P})

    w("PD6", {1: VBIAS, 2: BIAS})
    w("PZ4", {1: VBIAS, 2: HV_N})

    w("PD7", {1: V5, 2: SEC})               # secondary rectifier
    w("PZ5", {1: V5, 2: GND})

    w("PC9", {1: FB_A, 2: FB_K, 3: HV_N, 4: "EN_UV"})
    w("U21", {1: FB_REF, 2: GND, 3: FB_K})
    w("PR3", {1: V5, 2: FB_A})
    w("PR4", {1: V5, 2: FB_REF})
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# stay on the mains side of the isolation barrier and keep a mains-grade gap to
# anything SELV - but between themselves they carry tens of milliamps, not the
# 6 A a switched load does. Forcing 1.5 mm track and 2.0 mm clearance on the
# BYPASS pin decoupling makes the primary physically unroutable while buying no
# safety at all: 0.5 mm at 325 V is comfortable functional insulation, and the
# separation that actually matters is primary-to-secondary, which the barrier
# and the reinforced-creepage rule enforce independently.
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        return None

    def silk_text(layer, cx, cy, txt, size, thick):
        """Nudge a label off any pad it lands on; drop it if there is no room."""
        tw, th = len(txt) * size * 1.1 + 0.6, size + 0.6
        for dy in (0, 1.2, -1.2, 2.4, -2.4, 3.6, -3.6):
            y = cy + dy
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
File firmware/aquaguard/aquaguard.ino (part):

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/* 2.2.0  A latched dry run can be cleared again. The guard returned before the only line that reset it and there was no resetDryRun action, so one trip - often a false one on a slow inflow - killed the pump until somebody cut power. A user-initiated start now clears it; automation still cannot. */
/*
 * 2.3.0  The manual override no longer fires throughout the reset gesture.
 *        BTN_PIN is GPIO0, shared with `setResetButton(0)`, and the test was a
 *        level read with a 500 ms rate limit — so holding BOOT to change the
 *        Wi-Fi ran the override about six times, each pulsing the pump and
 *        setting `autoMode = false`. Auto-fill stayed off afterwards and the
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// Identical firmware — Wi-Fi + identity are provisioned by the Circuvent app.

// ---- pins ----
#define MOTOR_RELAY 26   // -> contactor coil
#define US_TRIG     25
#define US_ECHO     27
#define FLOAT_LOW   32   // active-low
#define FLOAT_HIGH  33   // active-low (overflow)
#define BTN_PIN      0
#define BUZZER_PIN   4
#define LED_PIN      2

// ---- tank geometry (cm) ----
float TANK_EMPTY_CM = 120.0;  // sensor-to-water distance when empty
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float distanceCm = 0;
uint32_t pumpStart = 0, lastStop = 0, lastBeep = 0;

void beep(int ms) { digitalWrite(BUZZER_PIN, HIGH); delay(ms); digitalWrite(BUZZER_PIN, LOW); }

void loadCfg() {
  store.begin("aqua", false);
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  if (on && (overflow || dryRun)) {
    pump = false;
    digitalWrite(MOTOR_RELAY, cvRelayLevel(false));
    digitalWrite(LED_PIN, LOW);
    cv.set("pump", pump);
    return;
  }
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  if (!on && pump) lastStop = millis();
  pump = on;
  cvRelayWrite(MOTOR_RELAY, on);
  digitalWrite(LED_PIN, on ? HIGH : LOW);
  cv.set("pump", pump);
}

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
void setup() {
  Serial.begin(115200);
  cvRelayInit(MOTOR_RELAY); pinMode(LED_PIN, OUTPUT); pinMode(BUZZER_PIN, OUTPUT);
  pinMode(US_TRIG, OUTPUT); pinMode(US_ECHO, INPUT);
  pinMode(FLOAT_LOW, INPUT_PULLUP); pinMode(FLOAT_HIGH, INPUT_PULLUP);
  pinMode(BTN_PIN, INPUT_PULLUP);
  btn.begin(BTN_PIN);
  loadCfg();
  level = computeLevel();
  setPump(pumpIntent);
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   * Manual override — on release, and only for a tap.
   *
   * "long-safe debounce" it was not: a level test with a 500 ms rate limit
   * re-fires twice a second for the whole press. BTN_PIN is GPIO0, the pin the
   * platform reset gesture uses, so holding BOOT for three seconds to change
   * the Wi-Fi ran this six times — each one setting `autoMode = false` and
   * pulsing the pump. Auto-fill was left off afterwards and stayed off, so the
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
